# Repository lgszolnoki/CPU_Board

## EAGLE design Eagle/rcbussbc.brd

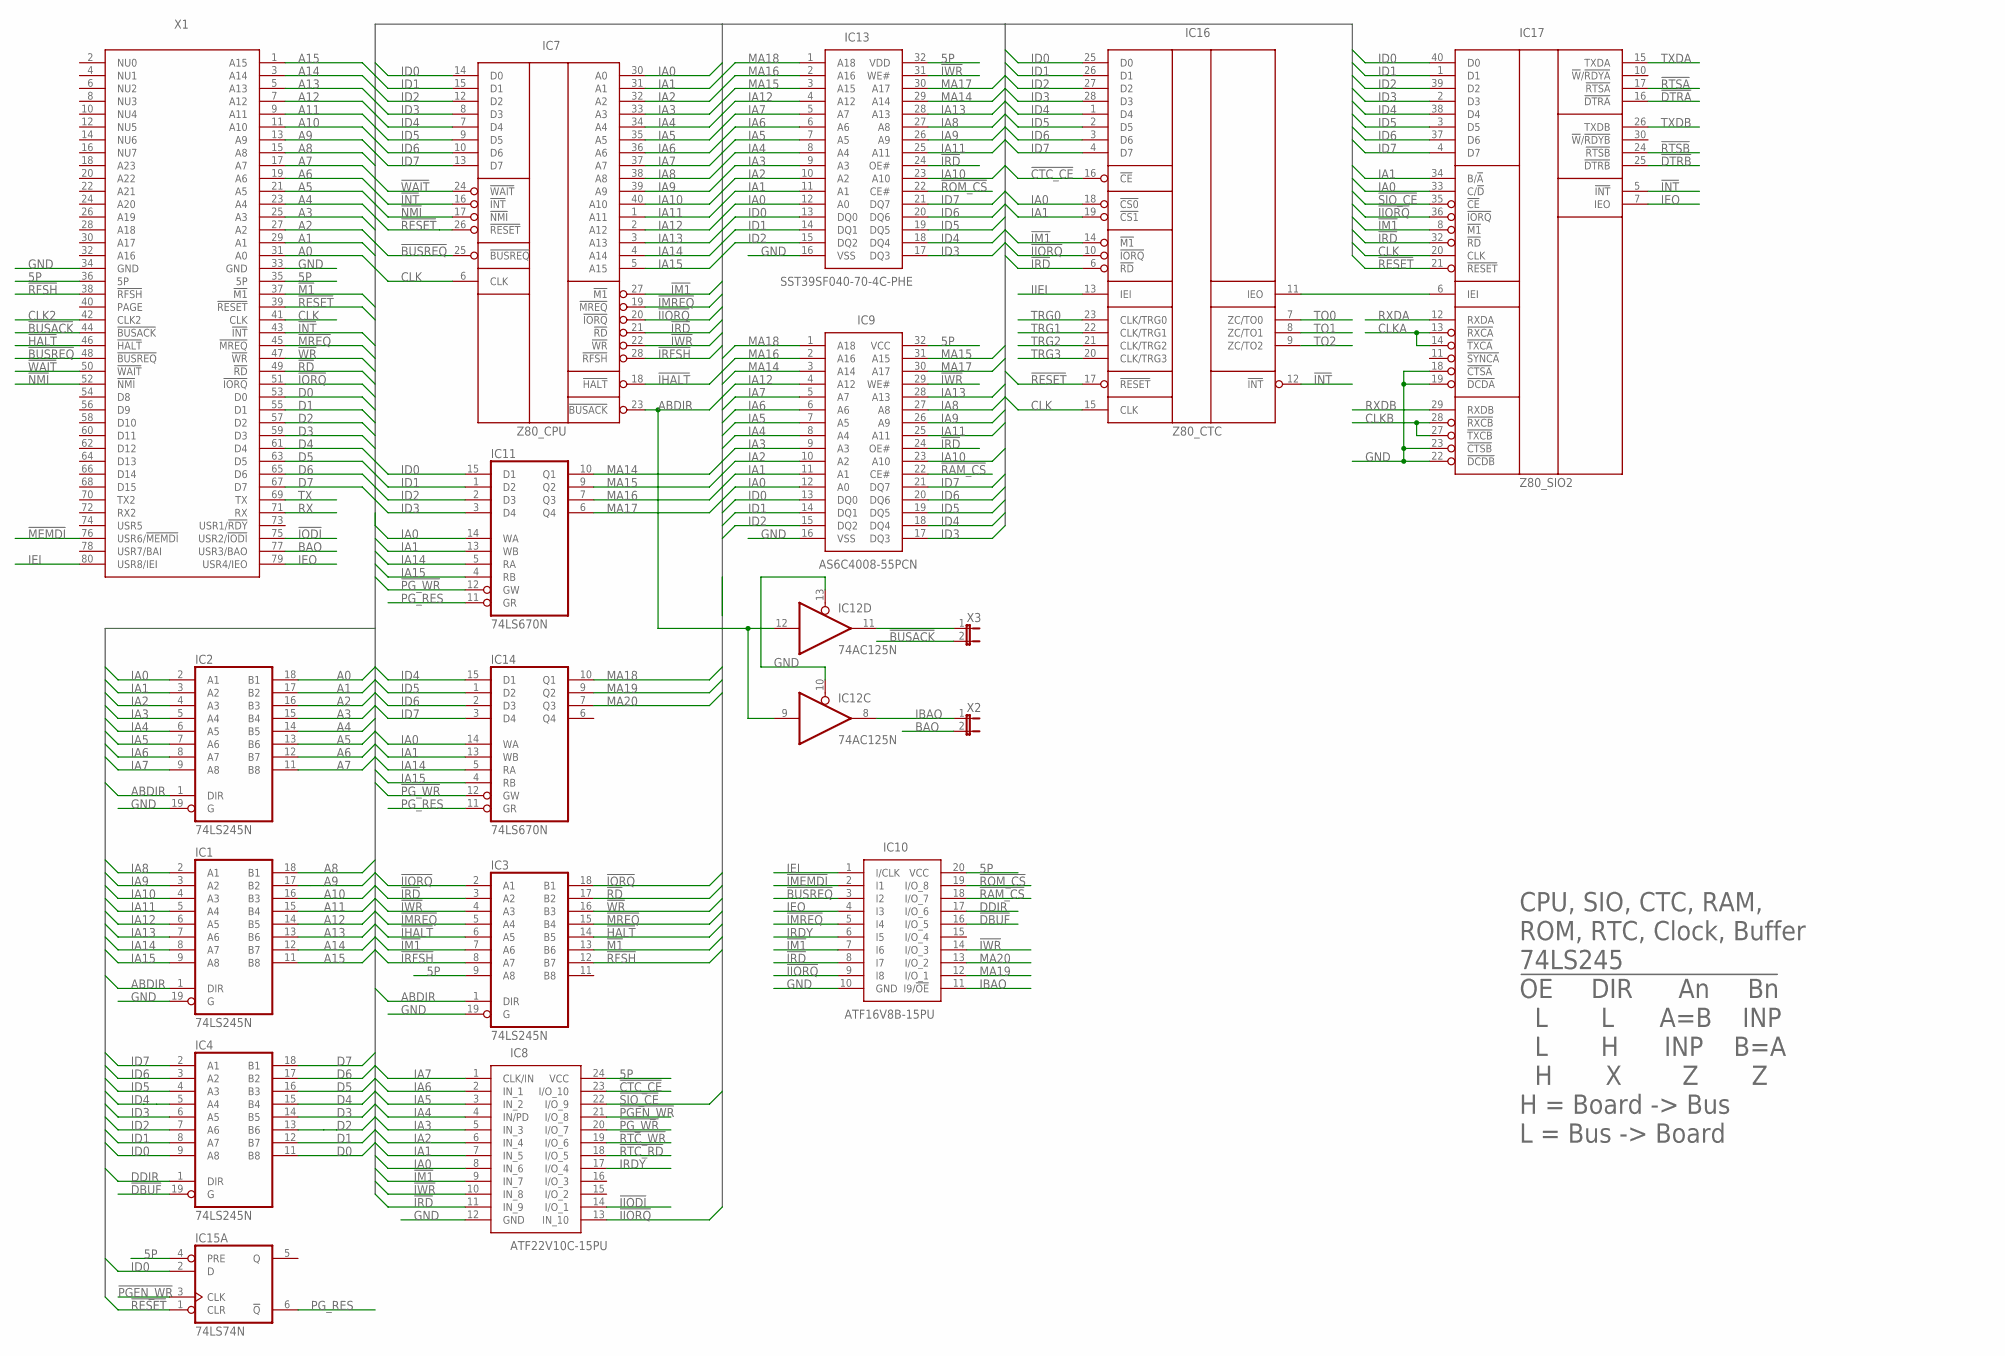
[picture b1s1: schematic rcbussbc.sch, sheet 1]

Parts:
IC1, IC2, IC3, IC4: 74LS245N; DIL20
IC7: Z80_CPU; DIP1612W53P254L5232H406Q40N
IC8: ATF22V10C-15PU; DIP794W56P254L3188H533Q24N
IC9: AS6C4008-55PCN; DIP1524W58P254L4191H406Q32N
IC10: ATF16V8B-15PU; DIP794W59P254L2591H533Q20N
IC11, IC14: 74LS670N; DIL16
IC12: 74AC125N; DIL14
IC13: SST39SF040-70-4C-PHE; DIP1556W56P254L4191H508Q32N
IC15: 74LS74N; DIL14
IC16: Z80_CTC; DIL28
IC17: Z80_SIO2; DIP1612W53P254L5232H406Q40N
X1: RCBUS_80_RA; RC2014_80_RA
X2, X3: JP1E; JP1

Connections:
5P: IC3.9 (A8), IC8.24 (VCC), IC9.32 (VCC), IC10.20 (VCC), IC13.32 (VDD), IC15.4 (PRE), X1.35 (5P), X1.36 (5P); also elsewhere on the board
!BUSACK: X1.44 (!BUSACK), X3.2
!BUSREQ: IC7.25 (!BUSREQ), IC10.3 (I2), X1.48 (!BUSREQ)
!CTC_CE: IC8.23 (I/O_10), IC16.16 (!CE)
!DBUF: IC4.19 (G), IC10.16 (I/O_5)
!DTRA: IC17.16 (!DTRA); also elsewhere on the board
!DTRB: IC17.25 (!DTRB); also elsewhere on the board
!HALT: IC3.14 (B5), X1.46 (!HALT)
!IHALT: IC3.6 (A5), IC7.18 (!HALT)
!IIODI: IC8.14 (I/O_1); also elsewhere on the board
!IIORQ: IC3.2 (A1), IC7.20 (!IORQ), IC8.13 (IN_10), IC10.9 (I8), IC16.10 (!IORQ), IC17.36 (!IORQ)
!IM1: IC3.7 (A6), IC7.27 (!M1), IC8.9 (IN_7), IC10.7 (I6), IC16.14 (!M1), IC17.8 (!M1)
!IMEMDI: IC10.2 (I1); also elsewhere on the board
!IMREQ: IC3.5 (A4), IC7.19 (!MREQ), IC10.5 (I4)
!INT: IC7.16 (!INT), IC16.12 (!INT), IC17.5 (!INT), X1.43 (!INT)
!IODI: X1.75 (USR2/!IODI); also elsewhere on the board
!IORQ: IC3.18 (B1), X1.51 (!IORQ)
!IRD: IC3.3 (A2), IC7.21 (!RD), IC8.11 (IN_9), IC9.24 (OE#), IC10.8 (I7), IC13.24 (OE#), IC16.6 (!RD), IC17.32 (!RD)
!IRFSH: IC3.8 (A7), IC7.28 (!RFSH)
!IWR: IC3.4 (A3), IC7.22 (!WR), IC8.10 (IN_8), IC9.29 (WE#), IC10.14 (I/O_3), IC13.31 (WE#)
!M1: IC3.13 (B6), X1.37 (!M1)
!MEMDI: X1.76 (USR6/!MEMDI); also elsewhere on the board
!MREQ: IC3.15 (B4), X1.45 (!MREQ)
!NMI: IC7.17 (!NMI), X1.52 (!NMI)
!PGEN_WR: IC8.21 (I/O_8), IC15.3 (CLK)
!PG_WR: IC8.20 (I/O_7), IC11.12 (GW), IC14.12 (GW)
!RAM_CS: IC9.22 (CE#), IC10.18 (I/O_7)
!RD: IC3.17 (B2), X1.49 (!RD)
!RESET: IC7.26 (!RESET), IC15.1 (CLR), IC16.17 (!RESET), IC17.21 (!RESET), X1.39 (!RESET); also elsewhere on the board
!RFSH: IC3.12 (B7), X1.38 (!RFSH)
!ROM_CS: IC10.19 (I/O_8), IC13.22 (CE#)
!RTC_RD: IC8.18 (I/O_5); also elsewhere on the board
!RTC_WR: IC8.19 (I/O_6); also elsewhere on the board
!RTSA: IC17.17 (!RTSA); also elsewhere on the board
!RTSB: IC17.24 (!RTSB); also elsewhere on the board
!SIO_CE: IC8.22 (I/O_9), IC17.35 (!CE)
!WAIT: IC7.24 (!WAIT), X1.50 (!WAIT)
!WR: IC3.16 (B3), X1.47 (!WR)
A0: IC2.18 (B1), X1.31 (A0)
A1: IC2.17 (B2), X1.29 (A1)
A2: IC2.16 (B3), X1.27 (A2)
A3: IC2.15 (B4), X1.25 (A3)
A4: IC2.14 (B5), X1.23 (A4)
A5: IC2.13 (B6), X1.21 (A5)
A6: IC2.12 (B7), X1.19 (A6)
A7: IC2.11 (B8), X1.17 (A7)
A8: IC1.18 (B1), X1.15 (A8)
A9: IC1.17 (B2), X1.13 (A9)
A10: IC1.16 (B3), X1.11 (A10)
A11: IC1.15 (B4), X1.9 (A11)
A12: IC1.14 (B5), X1.7 (A12)
A13: IC1.13 (B6), X1.5 (A13)
A14: IC1.12 (B7), X1.3 (A14)
A15: IC1.11 (B8), X1.1 (A15)
ABDIR: IC1.1 (DIR), IC2.1 (DIR), IC3.1 (DIR), IC7.23 (!BUSACK), IC12.9 (I), IC12.12 (I)
BAO: X1.77 (USR3/BAO), X2.2
CLK: IC7.6 (CLK), IC16.15 (CLK), IC17.20 (CLK), X1.41 (CLK); also elsewhere on the board
CLK2: X1.42 (CLK2); also elsewhere on the board
CLKA: IC17.13 (!RXCA), IC17.14 (!TXCA); also elsewhere on the board
CLKB: IC17.27 (!TXCB), IC17.28 (!RXCB); also elsewhere on the board
D0: IC4.11 (B8), X1.53 (D0)
D1: IC4.12 (B7), X1.55 (D1)
D2: IC4.13 (B6), X1.57 (D2)
D3: IC4.14 (B5), X1.59 (D3)
D4: IC4.15 (B4), X1.61 (D4)
D5: IC4.16 (B3), X1.63 (D5)
D6: IC4.17 (B2), X1.65 (D6)
D7: IC4.18 (B1), X1.67 (D7)
DDIR: IC4.1 (DIR), IC10.17 (I/O_6)
GND: IC1.19 (G), IC2.19 (G), IC3.19 (G), IC8.12 (GND), IC9.16 (VSS), IC10.10 (GND), IC12.10 (OE), IC12.13 (OE), IC13.16 (VSS), IC17.18 (!CTSA), IC17.19 (!DCDA), IC17.22 (!DCDB), IC17.23 (!CTSB), X1.33 (GND), X1.34 (GND); also elsewhere on the board
IA0: IC2.2 (A1), IC7.30 (A0), IC8.8 (IN_6), IC9.12 (A0), IC11.14 (WA), IC13.12 (A0), IC14.14 (WA), IC16.18 (!CS0), IC17.33 (C/!D)
IA1: IC2.3 (A2), IC7.31 (A1), IC8.7 (IN_5), IC9.11 (A1), IC11.13 (WB), IC13.11 (A1), IC14.13 (WB), IC16.19 (!CS1), IC17.34 (B/!A)
IA2: IC2.4 (A3), IC7.32 (A2), IC8.6 (IN_4), IC9.10 (A2), IC13.10 (A2)
IA3: IC2.5 (A4), IC7.33 (A3), IC8.5 (IN_3), IC9.9 (A3), IC13.9 (A3)
IA4: IC2.6 (A5), IC7.34 (A4), IC8.4 (IN/PD), IC9.8 (A4), IC13.8 (A4)
IA5: IC2.7 (A6), IC7.35 (A5), IC8.3 (IN_2), IC9.7 (A5), IC13.7 (A5)
IA6: IC2.8 (A7), IC7.36 (A6), IC8.2 (IN_1), IC9.6 (A6), IC13.6 (A6)
IA7: IC2.9 (A8), IC7.37 (A7), IC8.1 (CLK/IN), IC9.5 (A7), IC13.5 (A7)
IA8: IC1.2 (A1), IC7.38 (A8), IC9.27 (A8), IC13.27 (A8)
IA9: IC1.3 (A2), IC7.39 (A9), IC9.26 (A9), IC13.26 (A9)
IA10: IC1.4 (A3), IC7.40 (A10), IC9.23 (A10), IC13.23 (A10)
IA11: IC1.5 (A4), IC7.1 (A11), IC9.25 (A11), IC13.25 (A11)
IA12: IC1.6 (A5), IC7.2 (A12), IC9.4 (A12), IC13.4 (A12)
IA13: IC1.7 (A6), IC7.3 (A13), IC9.28 (A13), IC13.28 (A13)
IA14: IC1.8 (A7), IC7.4 (A14), IC11.5 (RA), IC14.5 (RA)
IA15: IC1.9 (A8), IC7.5 (A15), IC11.4 (RB), IC14.4 (RB)
IBAO: IC10.11 (I9/!OE), IC12.8 (O), X2.1
ID0: IC4.9 (A8), IC7.14 (D0), IC9.13 (DQ0), IC11.15 (D1), IC13.13 (DQ0), IC15.2 (D), IC16.25 (D0), IC17.40 (D0); also elsewhere on the board
ID1: IC4.8 (A7), IC7.15 (D1), IC9.14 (DQ1), IC11.1 (D2), IC13.14 (DQ1), IC16.26 (D1), IC17.1 (D1)
ID2: IC4.7 (A6), IC7.12 (D2), IC9.15 (DQ2), IC11.2 (D3), IC13.15 (DQ2), IC16.27 (D2), IC17.39 (D2)
ID3: IC4.6 (A5), IC7.8 (D3), IC9.17 (DQ3), IC11.3 (D4), IC13.17 (DQ3), IC16.28 (D3), IC17.2 (D3)
ID4: IC4.5 (A4), IC7.7 (D4), IC9.18 (DQ4), IC13.18 (DQ4), IC14.15 (D1), IC16.1 (D4), IC17.38 (D4); also elsewhere on the board
ID5: IC4.4 (A3), IC7.9 (D5), IC9.19 (DQ5), IC13.19 (DQ5), IC14.1 (D2), IC16.2 (D5), IC17.3 (D5); also elsewhere on the board
ID6: IC4.3 (A2), IC7.10 (D6), IC9.20 (DQ6), IC13.20 (DQ6), IC14.2 (D3), IC16.3 (D6), IC17.37 (D6); also elsewhere on the board
ID7: IC4.2 (A1), IC7.13 (D7), IC9.21 (DQ7), IC13.21 (DQ7), IC14.3 (D4), IC16.4 (D7), IC17.4 (D7); also elsewhere on the board
IEI: IC10.1 (I/CLK), X1.80 (USR8/IEI); also elsewhere on the board
IEO: IC10.4 (I3), IC17.7 (IEO), X1.79 (USR4/IEO)
IIEI: IC16.13 (IEI); also elsewhere on the board
IRDY: IC8.17 (I/O_4), IC10.6 (I5)
MA14: IC9.3 (A14), IC11.10 (Q1), IC13.29 (A14); also elsewhere on the board
MA15: IC9.31 (A15), IC11.9 (Q2), IC13.3 (A15); also elsewhere on the board
MA16: IC9.2 (A16), IC11.7 (Q3), IC13.2 (A16); also elsewhere on the board
MA17: IC9.30 (A17), IC11.6 (Q4), IC13.30 (A17); also elsewhere on the board
MA18: IC9.1 (A18), IC13.1 (A18), IC14.10 (Q1); also elsewhere on the board
MA19: IC10.12 (I/O_1), IC14.9 (Q2)
MA20: IC10.13 (I/O_2), IC14.7 (Q3)
unnamed: IC16.11 (IEO), IC17.6 (IEI)
unnamed: IC12.11 (O), X3.1
PG_RES: IC11.11 (GR), IC14.11 (GR), IC15.6 (!Q)
RX: X1.71 (RX); also elsewhere on the board
RXDA: IC17.12 (RXDA); also elsewhere on the board
RXDB: IC17.29 (RXDB); also elsewhere on the board
TO0: IC16.7 (ZC/TO0); also elsewhere on the board
TO1: IC16.8 (ZC/TO1); also elsewhere on the board
TO2: IC16.9 (ZC/TO2); also elsewhere on the board
TRG0: IC16.23 (CLK/TRG0); also elsewhere on the board
TRG1: IC16.22 (CLK/TRG1); also elsewhere on the board
TRG2: IC16.21 (CLK/TRG2); also elsewhere on the board
TRG3: IC16.20 (CLK/TRG3); also elsewhere on the board
TX: X1.69 (TX); also elsewhere on the board
TXDA: IC17.15 (TXDA); also elsewhere on the board
TXDB: IC17.26 (TXDB); also elsewhere on the board

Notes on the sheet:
CPU, SIO, CTC, RAM, ROM, RTC, Clock, Buffer 74LS245 !OE DIR An Bn L L A=B INP L H INP B=A H X Z Z H = Board -> Bus L = Bus -> Board

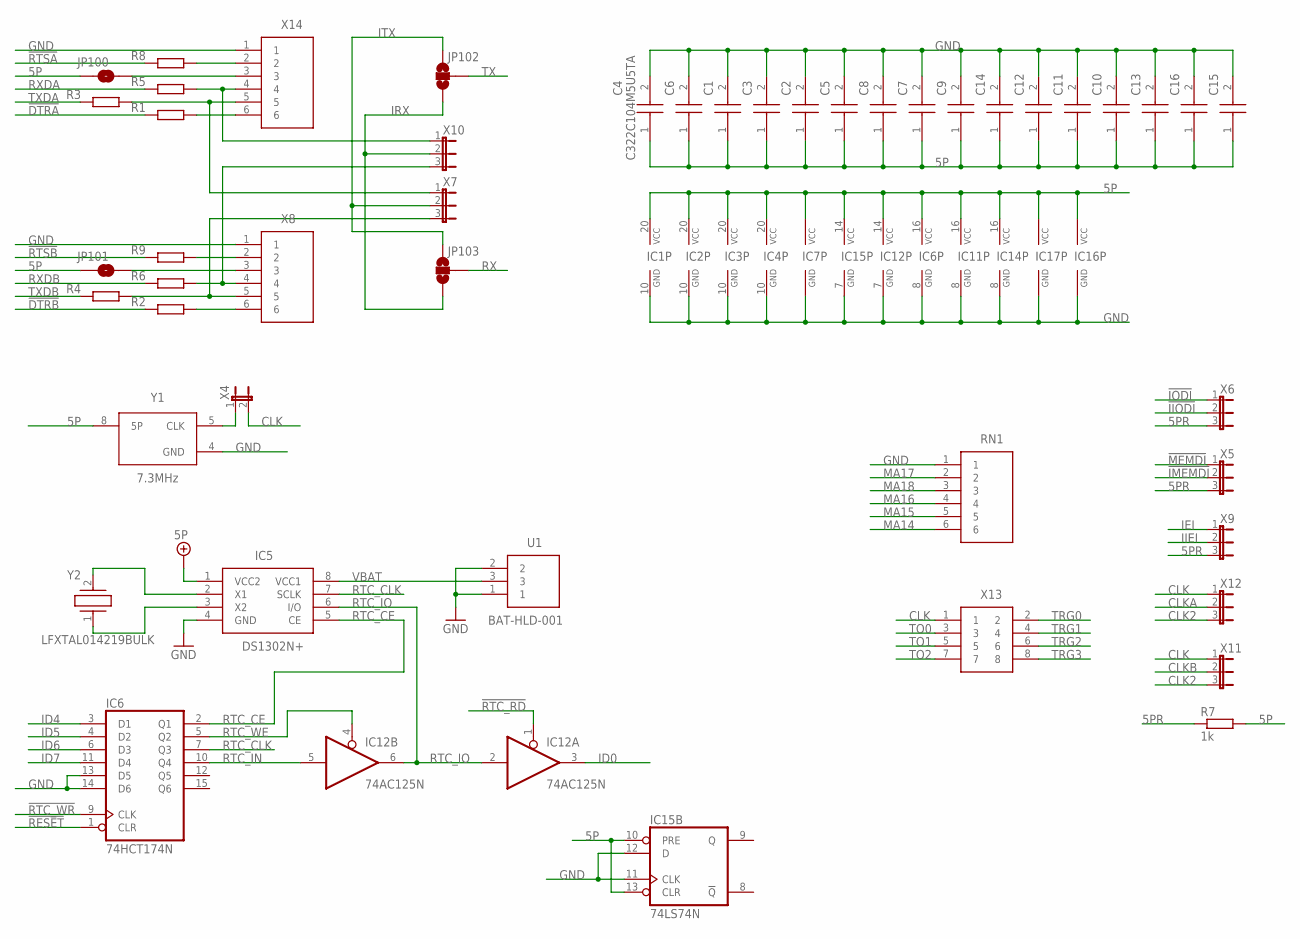
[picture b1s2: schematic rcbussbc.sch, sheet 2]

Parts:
C1, C2, C3, C4, C5, C6, C7, C8, C9, C10, C11, C12, C13, C14, C15, C16: C322C104M5U5TA; C322C104K1R5TA
IC1, IC2, IC3, IC4: 74LS245N; DIL20
IC5: DS1302N+; DIP762W56P254L938H457Q8N
IC6: 74HCT174N; DIL16
IC7: Z80_CPU; DIP1612W53P254L5232H406Q40N
IC11, IC14: 74LS670N; DIL16
IC12: 74AC125N; DIL14
IC15: 74LS74N; DIL14
IC16: Z80_CTC; DIL28
IC17: Z80_SIO2; DIP1612W53P254L5232H406Q40N
JP100, JP101: JUMPER-SMT_2_NO_SILK; SMT-JUMPER_2_NO_SILK
JP102, JP103: JUMPER-SMT_3_NO_SILK; SMT-JUMPER_3_NO_SILK
R1, R2, R3, R4, R5, R6, R7, R8, R9: 1k; 0207/10
RN1: 4606X-101-102LF; 4606X101102LF
U1: BAT-HLD-001; BATHLD001
X4: JP1E; JP1
X5, X6, X7, X9, X10, X11, X12: JP2E; JP2
X8, X14: TSW-106-08-T-S-RA; HDRRA6W64P254_1X6_1524X254X309
X13: 10129381-908002BLF; HDRV8W67P254_2X4_1016X483X858P
Y1: 7.3MHz; ECS-2100AX-200
Y2: LFXTAL014219BULK

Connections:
5P: C1.1 (+), C2.1 (+), C3.1 (+), C4.1 (+), C5.1 (+), C6.1 (+), C7.1 (+), C8.1 (+), C9.1 (+), C10.1 (+), C11.1 (+), C12.1 (+), C13.1 (+), C14.1 (+), C15.1 (+), C16.1 (+), IC1.20 (VCC), IC2.20 (VCC), IC3.20 (VCC), IC4.20 (VCC), IC5.1 (VCC2), IC6.16 (VCC), IC7.11 (VCC), IC11.16 (VCC), IC12.14 (VCC), IC14.16 (VCC), IC15.10 (PRE), IC15.13 (CLR), IC15.14 (VCC), IC16.24 (VCC), IC17.9 (VCC), JP100.1, JP101.1, R7.2, Y1.8 (5P); also elsewhere on the board
5PR: R7.1, X5.3, X6.3, X9.3
!DTRA: R1.1; also elsewhere on the board
!DTRB: R2.1; also elsewhere on the board
!IIODI: X6.2; also elsewhere on the board
!IMEMDI: X5.2; also elsewhere on the board
!IODI: X6.1; also elsewhere on the board
!MEMDI: X5.1; also elsewhere on the board
!RESET: IC6.1 (CLR); also elsewhere on the board
!RTC_RD: IC12.1 (OE); also elsewhere on the board
!RTC_WR: IC6.9 (CLK); also elsewhere on the board
!RTSA: R8.1; also elsewhere on the board
!RTSB: R9.1; also elsewhere on the board
CLK: X4.2, X11.1, X12.1, X13.1; also elsewhere on the board
CLK2: X11.3, X12.3; also elsewhere on the board
CLKA: X12.2; also elsewhere on the board
CLKB: X11.2; also elsewhere on the board
GND: C1.2 (-), C2.2 (-), C3.2 (-), C4.2 (-), C5.2 (-), C6.2 (-), C7.2 (-), C8.2 (-), C9.2 (-), C10.2 (-), C11.2 (-), C12.2 (-), C13.2 (-), C14.2 (-), C15.2 (-), C16.2 (-), IC1.10 (GND), IC2.10 (GND), IC3.10 (GND), IC4.10 (GND), IC5.4 (GND), IC6.8 (GND), IC6.13 (D5), IC6.14 (D6), IC7.29 (GND), IC11.8 (GND), IC12.7 (GND), IC14.8 (GND), IC15.7 (GND), IC15.11 (CLK), IC15.12 (D), IC16.5 (GND), IC17.31 (GND), RN1.1, U1.1, U1.2, X8.1, X14.1, Y1.4 (GND); also elsewhere on the board
ID0: IC12.3 (O); also elsewhere on the board
ID4: IC6.3 (D1); also elsewhere on the board
ID5: IC6.4 (D2); also elsewhere on the board
ID6: IC6.6 (D3); also elsewhere on the board
ID7: IC6.11 (D4); also elsewhere on the board
IEI: X9.1; also elsewhere on the board
IIEI: X9.2; also elsewhere on the board
IRX: JP102.1, JP103.1, X10.2
ITX: JP102.3, JP103.3, X7.2
MA14: RN1.6; also elsewhere on the board
MA15: RN1.5; also elsewhere on the board
MA16: RN1.4; also elsewhere on the board
MA17: RN1.2; also elsewhere on the board
MA18: RN1.3; also elsewhere on the board
unnamed: IC5.3 (X2), Y2.1
unnamed: X4.1, Y1.5 (CLK)
unnamed: JP100.2, X14.3
unnamed: R8.2, X14.2
unnamed: R5.2, X10.1, X14.4
unnamed: R3.2, X7.1, X14.5
unnamed: R1.2, X14.6
unnamed: JP101.2, X8.3
unnamed: R9.2, X8.2
unnamed: R6.2, X8.4, X10.3
unnamed: IC5.2 (X1), Y2.2
unnamed: R4.2, X7.3, X8.5
unnamed: R2.2, X8.6
RTC_CE: IC5.5 (CE), IC6.2 (Q1)
RTC_CLK: IC5.7 (SCLK), IC6.7 (Q3)
RTC_IN: IC6.10 (Q4), IC12.5 (I)
RTC_IO: IC5.6 (I/O), IC12.2 (I), IC12.6 (O)
RTC_WE: IC6.5 (Q2), IC12.4 (OE)
RX: JP103.2; also elsewhere on the board
RXDA: R5.1; also elsewhere on the board
RXDB: R6.1; also elsewhere on the board
TO0: X13.3; also elsewhere on the board
TO1: X13.5; also elsewhere on the board
TO2: X13.7; also elsewhere on the board
TRG0: X13.2; also elsewhere on the board
TRG1: X13.4; also elsewhere on the board
TRG2: X13.6; also elsewhere on the board
TRG3: X13.8; also elsewhere on the board
TX: JP102.2; also elsewhere on the board
TXDA: R3.1; also elsewhere on the board
TXDB: R4.1; also elsewhere on the board
VBAT: IC5.8 (VCC1), U1.3

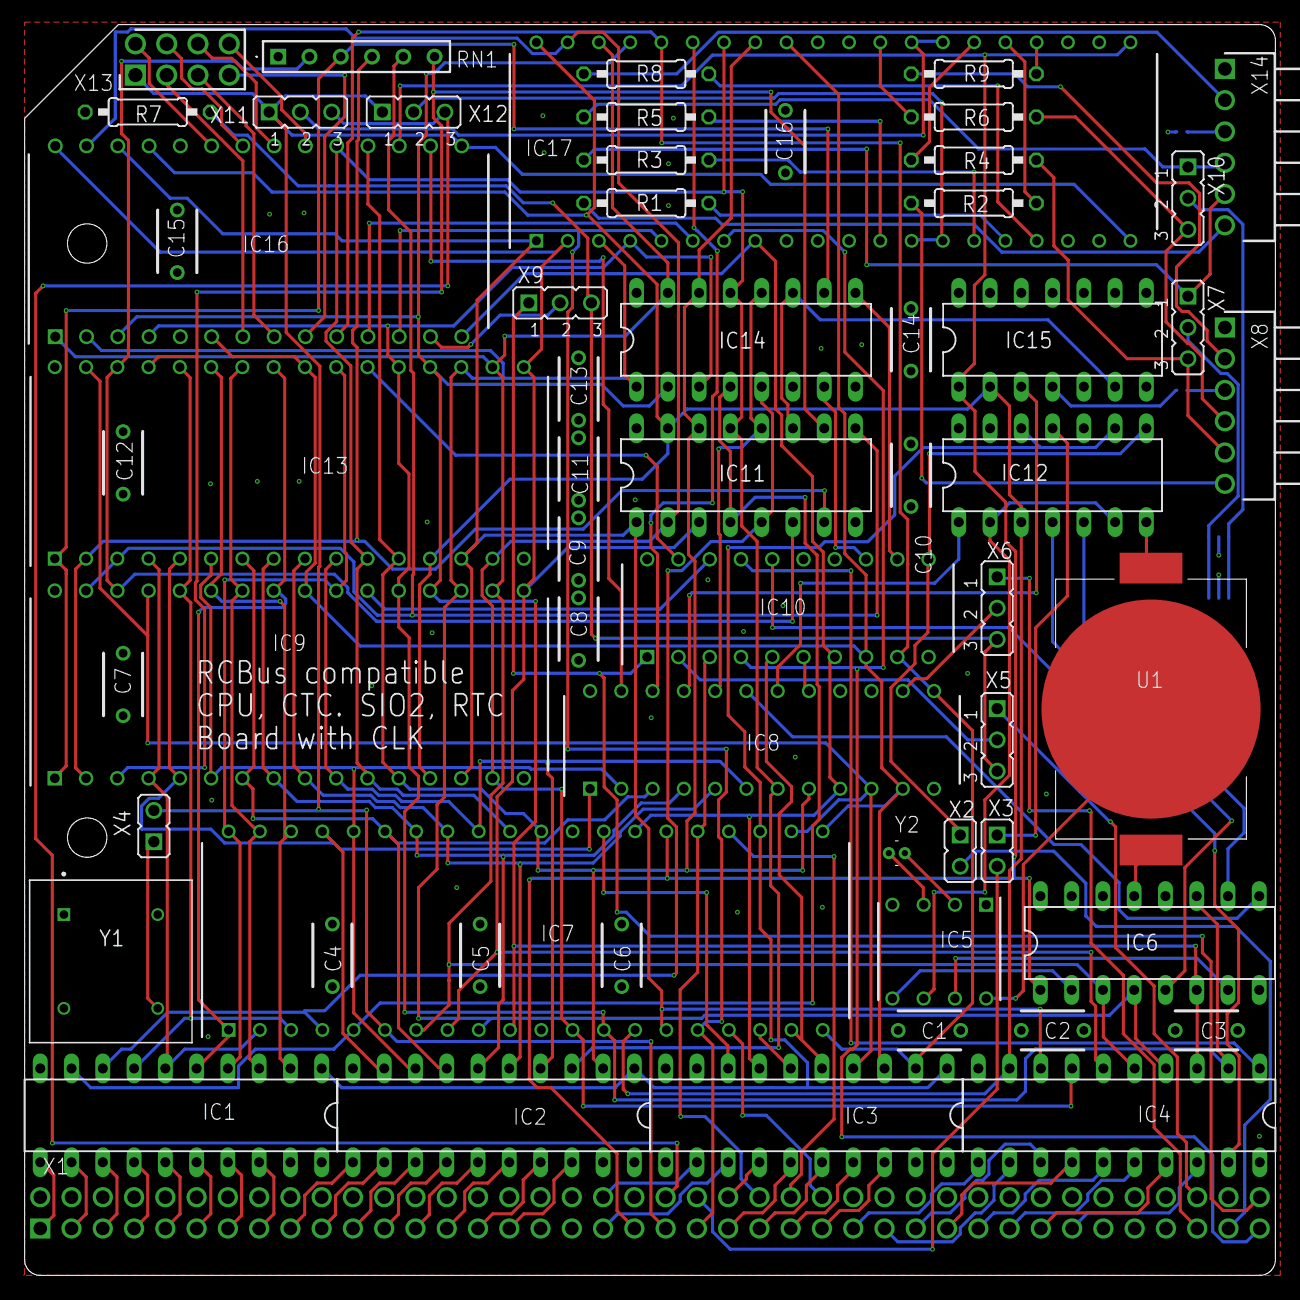
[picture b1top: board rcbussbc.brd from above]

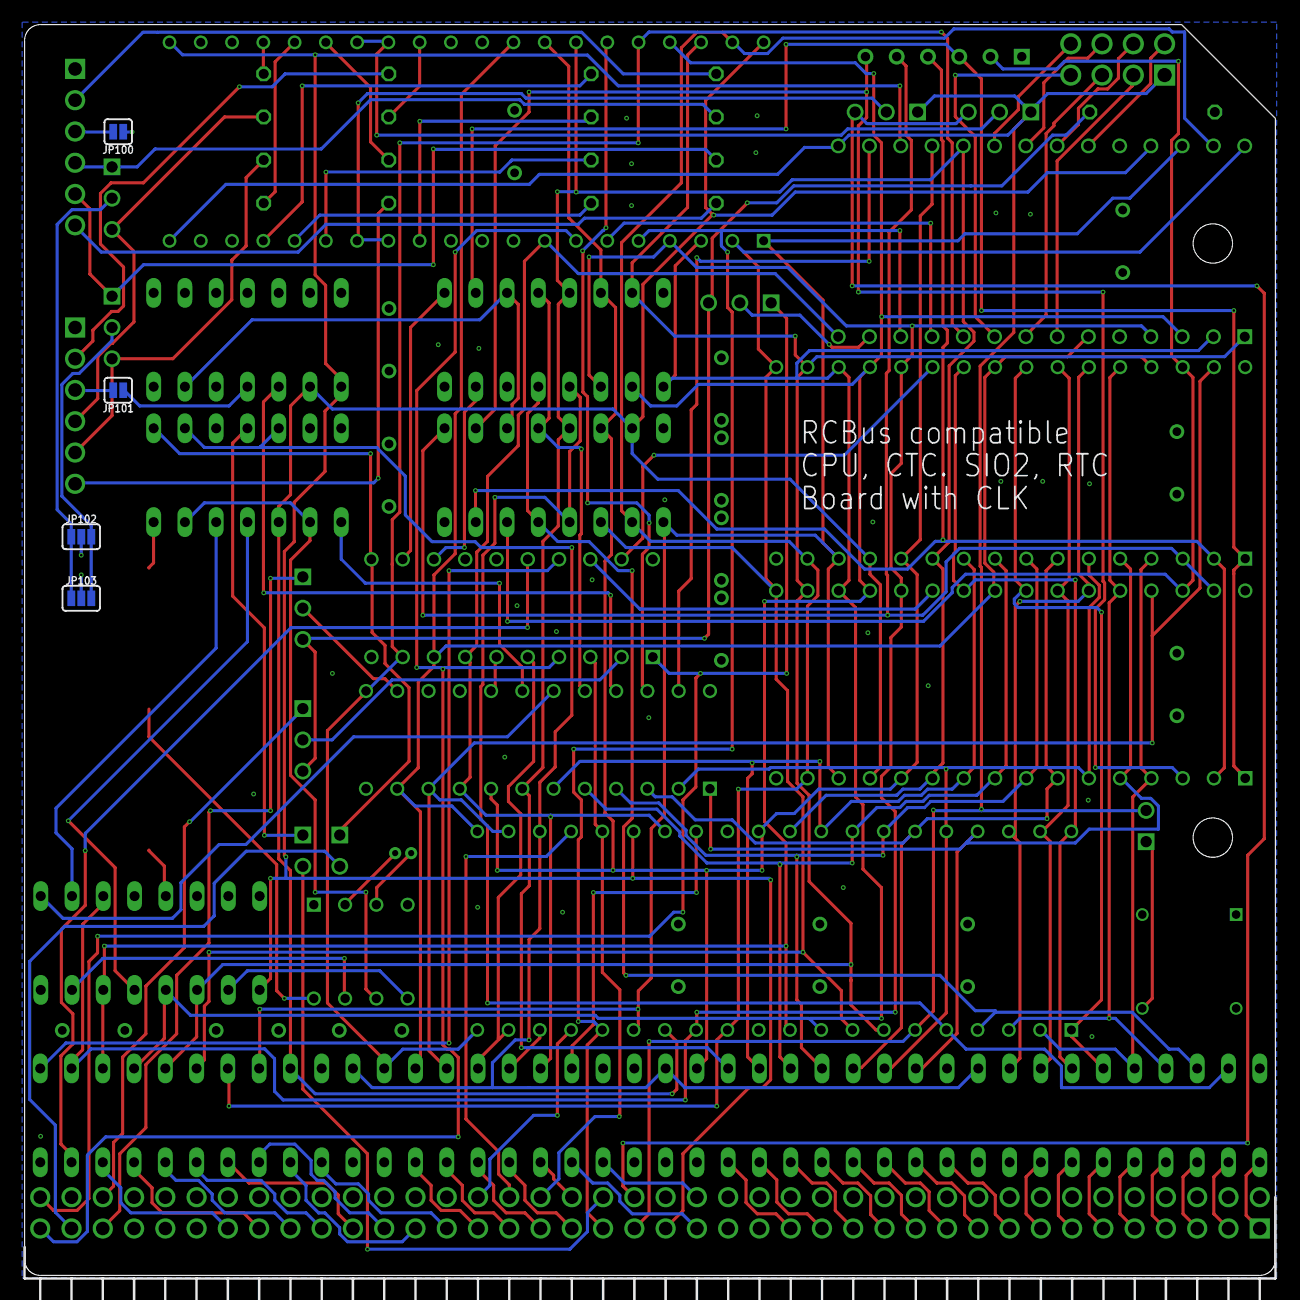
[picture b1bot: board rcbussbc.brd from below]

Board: 4 copper layers, 101.6 x 101.6 mm, 64 parts (4 on the bottom side), 144 nets.

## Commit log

2024-07-18 Rename ReadMe to ReadMe.md

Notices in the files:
parts and their libraries:
SparkFun-Jumpers: Licensing: Creative Commons ShareAlike 4.0 International - https://creativecommons.org/licenses/by-sa/4.0
